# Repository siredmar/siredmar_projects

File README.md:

siredmar_projects
=================

edmar_projects

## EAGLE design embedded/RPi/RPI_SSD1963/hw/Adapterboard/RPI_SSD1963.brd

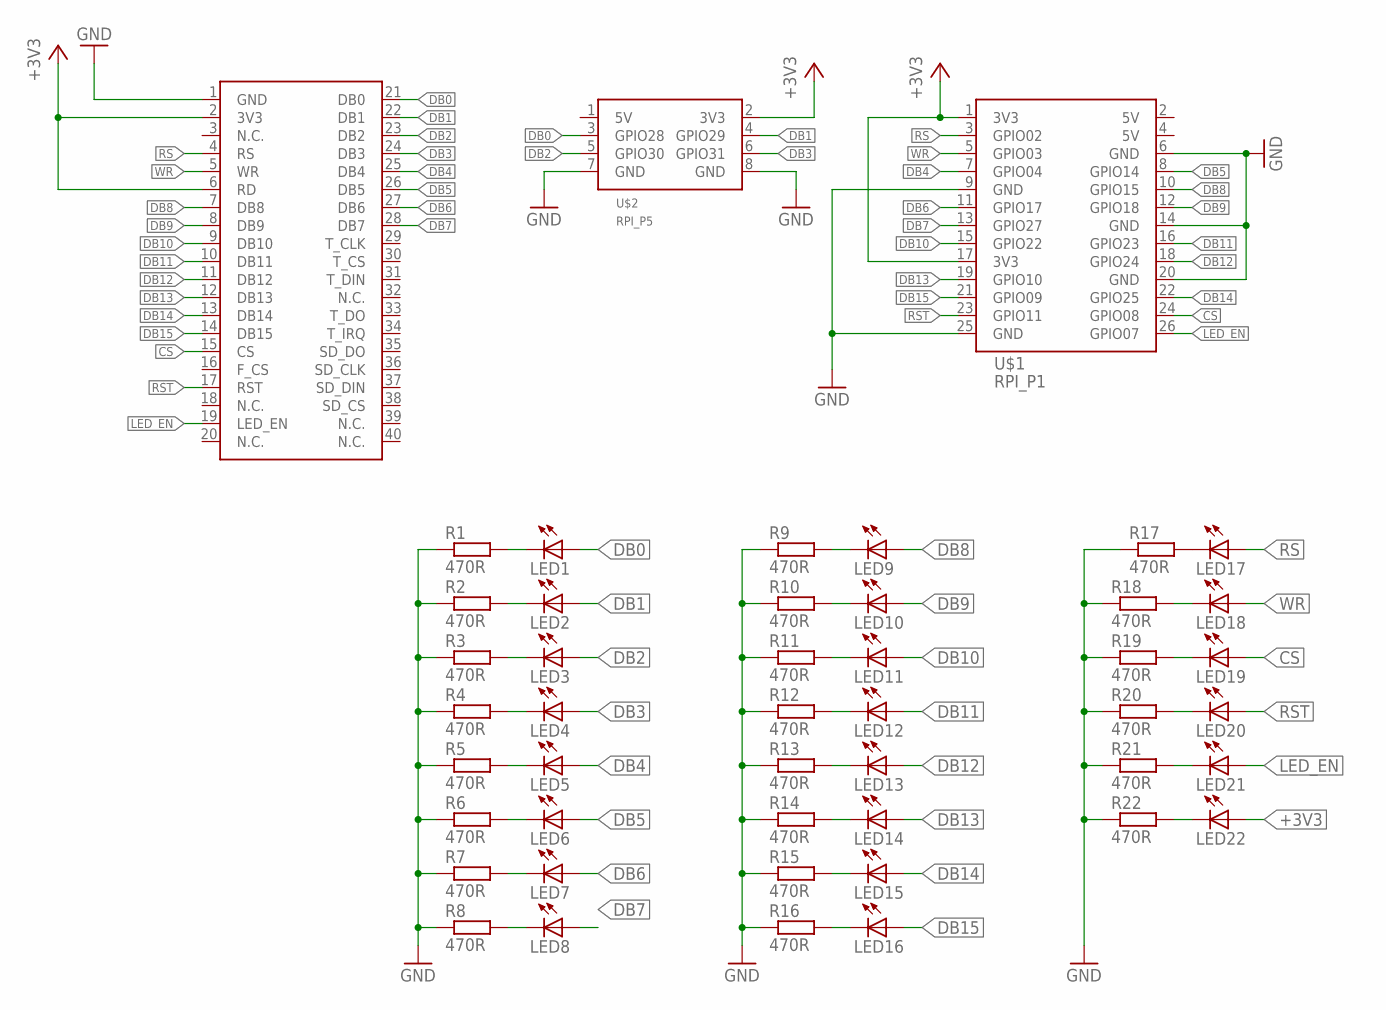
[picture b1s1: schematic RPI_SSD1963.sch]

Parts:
LED1, LED2, LED3, LED4, LED5, LED6, LED7, LED8, LED9, LED10, LED11, LED12, LED13, LED14, LED15, LED16, LED17, LED18, LED19, LED20, LED21, LED22: LEDCHIP-LED0603; CHIP-LED0603
R1, R2, R3, R4, R5, R6, R7, R8, R9, R10, R11, R12, R13, R14, R15, R16, R17, R18, R19, R20, R21, R22: 470R; R0402
U$1: RPI_P1
U$2: RPI_P5
U$3: SSD1963

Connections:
+3V3: LED22.A, U$1.1 (3V3), U$1.17 (3V3), U$2.2 (3V3), U$3.2 (3V3), U$3.6 (RD)
CS: LED19.A, U$1.24 (GPIO08), U$3.15 (CS)
DB0: LED1.A, U$2.3 (GPIO28), U$3.21 (DB0)
DB1: LED2.A, U$2.4 (GPIO29), U$3.22 (DB1)
DB2: LED3.A, U$2.5 (GPIO30), U$3.23 (DB2)
DB3: LED4.A, U$2.6 (GPIO31), U$3.24 (DB3)
DB4: LED5.A, U$1.7 (GPIO04), U$3.25 (DB4)
DB5: LED6.A, U$1.8 (GPIO14), U$3.26 (DB5)
DB6: LED7.A, U$1.11 (GPIO17), U$3.27 (DB6)
DB7: LED8.A, U$1.13 (GPIO27), U$3.28 (DB7)
DB8: LED9.A, U$1.10 (GPIO15), U$3.7 (DB8)
DB9: LED10.A, U$1.12 (GPIO18), U$3.8 (DB9)
DB10: LED11.A, U$1.15 (GPIO22), U$3.9 (DB10)
DB11: LED12.A, U$1.16 (GPIO23), U$3.10 (DB11)
DB12: LED13.A, U$1.18 (GPIO24), U$3.11 (DB12)
DB13: LED14.A, U$1.19 (GPIO10), U$3.12 (DB13)
DB14: LED15.A, U$1.22 (GPIO25), U$3.13 (DB14)
DB15: LED16.A, U$1.21 (GPIO09), U$3.14 (DB15)
GND: R1.1, R2.1, R3.1, R4.1, R5.1, R6.1, R7.1, R8.1, R9.1, R10.1, R11.1, R12.1, R13.1, R14.1, R15.1, R16.1, R17.1, R18.1, R19.1, R20.1, R21.1, R22.1, U$1.6 (GND), U$1.9 (GND), U$1.14 (GND), U$1.20 (GND), U$1.25 (GND), U$2.7 (GND), U$2.8 (GND), U$3.1 (GND)
LED_EN: LED21.A, U$1.26 (GPIO07), U$3.19 (LED_EN)
unnamed: LED1.C, R1.2
unnamed: LED2.C, R2.2
unnamed: LED3.C, R3.2
unnamed: LED4.C, R4.2
unnamed: LED5.C, R5.2
unnamed: LED6.C, R6.2
unnamed: LED7.C, R7.2
unnamed: LED8.C, R8.2
unnamed: LED9.C, R9.2
unnamed: LED10.C, R10.2
unnamed: LED11.C, R11.2
unnamed: LED12.C, R12.2
unnamed: LED13.C, R13.2
unnamed: LED14.C, R14.2
unnamed: LED15.C, R15.2
unnamed: LED16.C, R16.2
unnamed: LED17.C, R17.2
unnamed: LED18.C, R18.2
unnamed: LED19.C, R19.2
unnamed: LED20.C, R20.2
unnamed: LED21.C, R21.2
unnamed: LED22.C, R22.2
RS: LED17.A, U$1.3 (GPIO02), U$3.4 (RS)
RST: LED20.A, U$1.23 (GPIO11), U$3.17 (RST)
WR: LED18.A, U$1.5 (GPIO03), U$3.5 (WR)

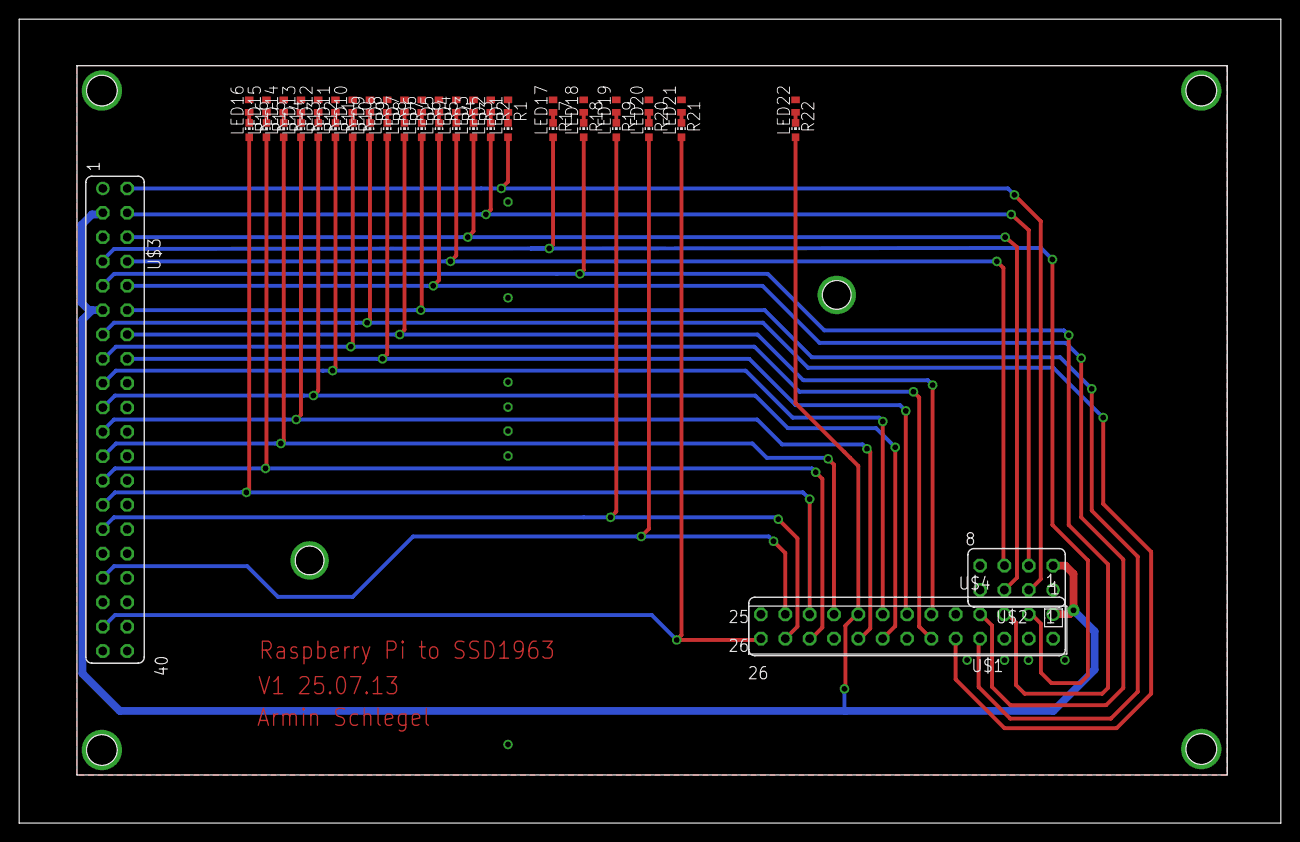
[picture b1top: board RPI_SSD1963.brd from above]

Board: 2 copper layers, 131.6 x 83.9 mm, 48 parts (0 on the bottom side), 45 nets.

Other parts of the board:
U$4: RPI_OUTLINE; RASP_OUTLINE

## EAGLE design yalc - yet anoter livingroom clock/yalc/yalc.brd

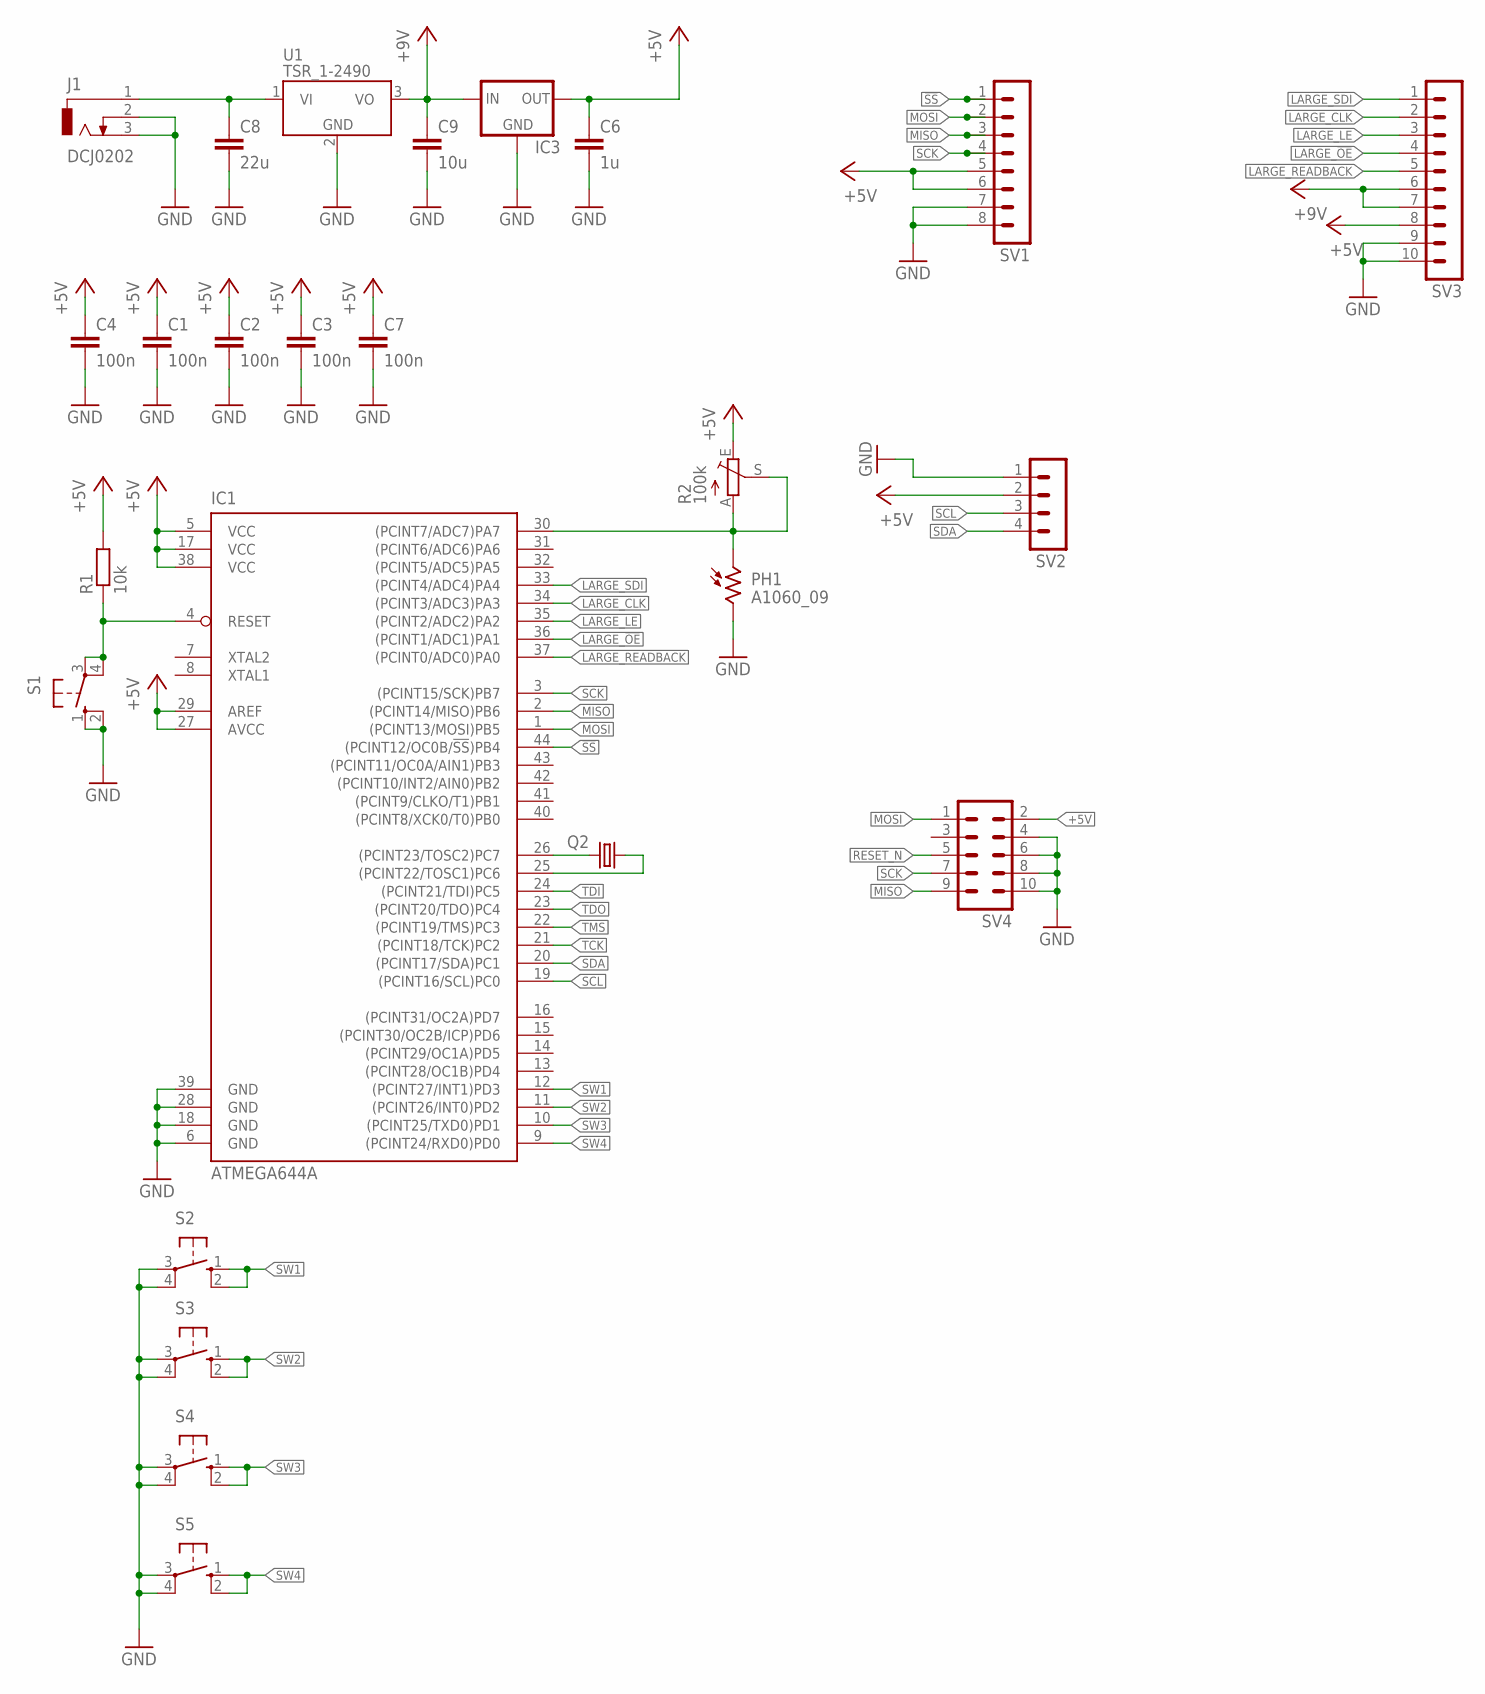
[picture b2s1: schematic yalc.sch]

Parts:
C1, C2, C3, C4, C7: 100n; C0805
C6: 1u; C1206K
C8: 22u; C1206K
C9: 10u; C1206K
IC1: ATMEGA644A; TQFP44
IC3: LFXXCVL; TO220L1
J1: DCJ0202
PH1: A1060_09; T0-46-A10XX
Q2: CRYSTALTC26H; TC26H
R1: 10k; R0805
R2: 100k; ECP10S
S1, S2, S3, S4, S5: 10-XX; B3F-10XX
SV1: MA08-1W
SV2: MA04-1
SV3: MA10-1W
SV4: ML10
U1: TSR_1-2490; TSR-1

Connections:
!SS: IC1.44 ((PCINT12/OC0B/!SS!)PB4), SV1.1
+5V: C1.1, C2.1, C3.1, C4.1, C6.1, C7.1, IC1.5 (VCC), IC1.17 (VCC), IC1.27 (AVCC), IC1.29 (AREF), IC1.38 (VCC), IC3.3 (OUT), R1.2, R2.E, SV1.5, SV1.6, SV2.2, SV3.8, SV4.2
+9V: C9.1, IC3.1 (IN), SV3.6, SV3.7, U1.3 (VO)
GND: C1.2, C2.2, C3.2, C4.2, C6.2, C7.2, C8.2, C9.2, IC1.6 (GND), IC1.18 (GND), IC1.28 (GND), IC1.39 (GND), IC3.2 (GND), J1.2, J1.3, PH1.2, S1.1 (S), S1.2 (S1), S2.3, S2.4 (P1), S3.3, S3.4 (P1), S4.3, S4.4 (P1), S5.3, S5.4 (P1), SV1.7, SV1.8, SV2.1, SV3.9, SV3.10, SV4.4, SV4.6, SV4.8, SV4.10, U1.2 (GND)
LARGE_!OE: IC1.36 ((PCINT1/ADC1)PA1), SV3.4
LARGE_CLK: IC1.34 ((PCINT3/ADC3)PA3), SV3.2
LARGE_LE: IC1.35 ((PCINT2/ADC2)PA2), SV3.3
LARGE_READBACK: IC1.37 ((PCINT0/ADC0)PA0), SV3.5
LARGE_SDI: IC1.33 ((PCINT4/ADC4)PA4), SV3.1
MISO: IC1.2 ((PCINT14/MISO)PB6), SV1.3, SV4.9
MOSI: IC1.1 ((PCINT13/MOSI)PB5), SV1.2, SV4.1
unnamed: IC1.30 ((PCINT7/ADC7)PA7), PH1.1, R2.A, R2.S
unnamed: IC1.26 ((PCINT23/TOSC2)PC7), Q2.2
unnamed: IC1.25 ((PCINT22/TOSC1)PC6), Q2.1
RESET_N: IC1.4 (RESET), R1.1, S1.3, S1.4 (P1), SV4.5
SCK: IC1.3 ((PCINT15/SCK)PB7), SV1.4, SV4.7
SCL: IC1.19 ((PCINT16/SCL)PC0), SV2.3
SDA: IC1.20 ((PCINT17/SDA)PC1), SV2.4
SW1: IC1.12 ((PCINT27/INT1)PD3), S2.1 (S), S2.2 (S1)
SW2: IC1.11 ((PCINT26/INT0)PD2), S3.1 (S), S3.2 (S1)
SW3: IC1.10 ((PCINT25/TXD0)PD1), S4.1 (S), S4.2 (S1)
SW4: IC1.9 ((PCINT24/RXD0)PD0), S5.1 (S), S5.2 (S1)
TCK: IC1.21 ((PCINT18/TCK)PC2)
TDI: IC1.24 ((PCINT21/TDI)PC5)
TDO: IC1.23 ((PCINT20/TDO)PC4)
TMS: IC1.22 ((PCINT19/TMS)PC3)
VI: C8.1, J1.1, U1.1 (VI)

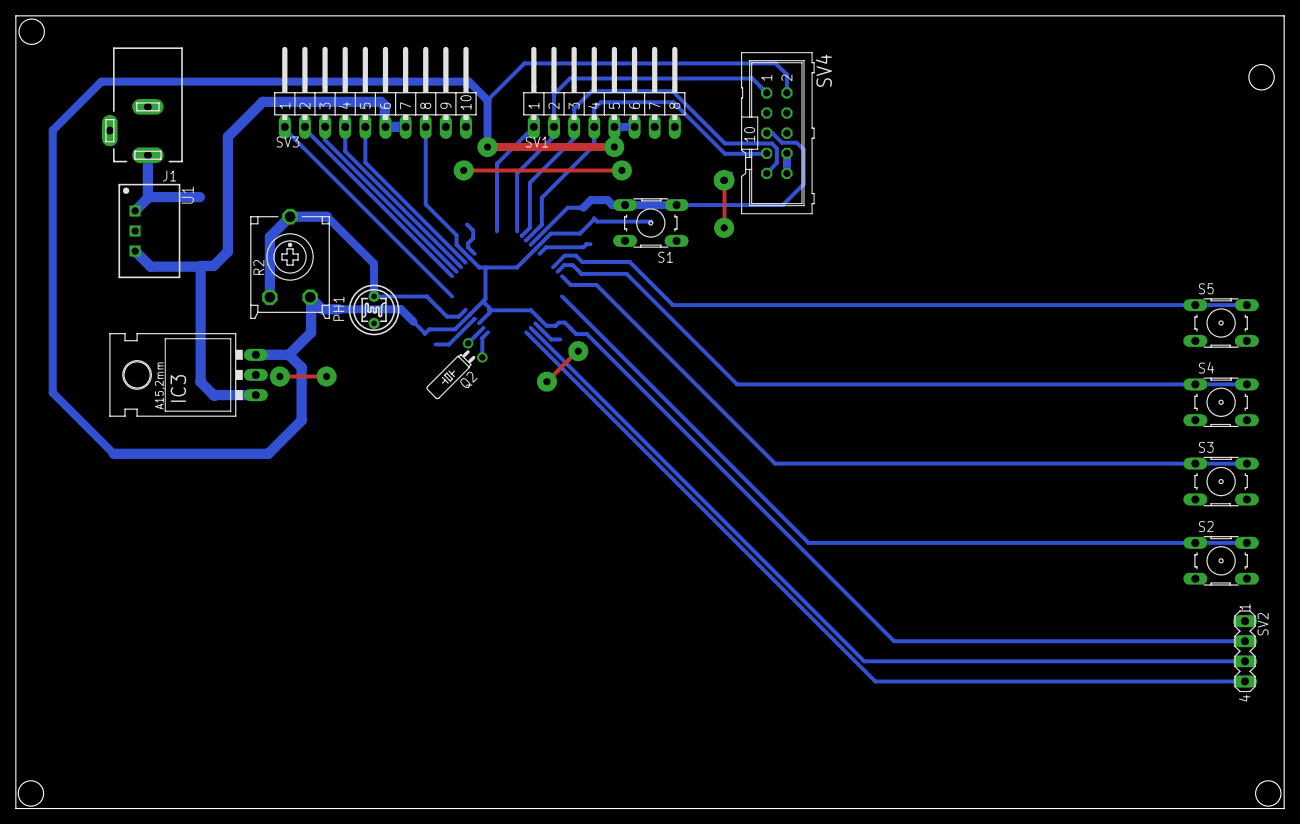
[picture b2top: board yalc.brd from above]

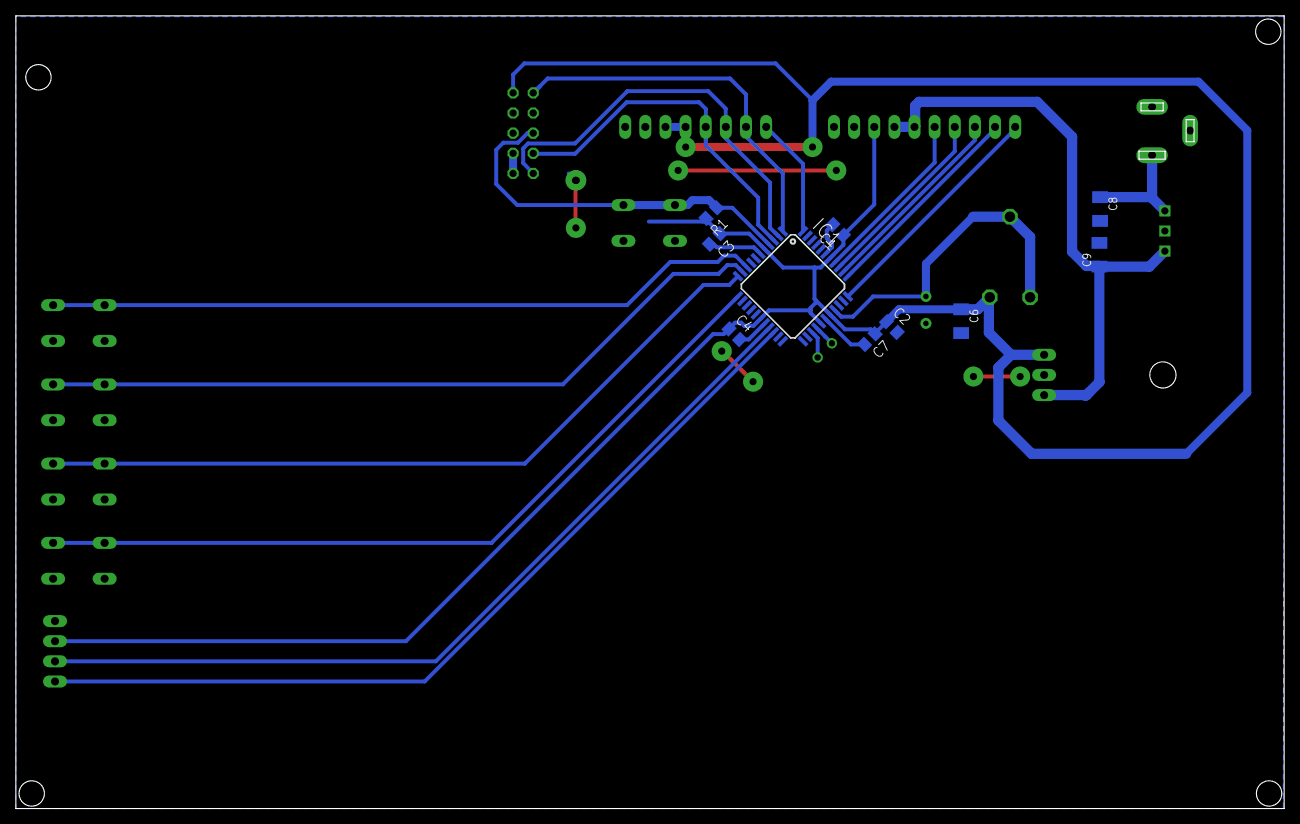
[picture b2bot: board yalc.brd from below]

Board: 2 copper layers, 160.0 x 100.0 mm, 25 parts (10 on the bottom side), 23 nets.

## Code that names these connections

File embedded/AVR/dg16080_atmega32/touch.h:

/**
 * touch.h
 *
 *  Created on: 29.05.2009
 *      Author: sebastian
 */

#ifndef TOUCH_H_
#define TOUCH_H_ TOUCH_H_

#include "adc.h"


#define TOUCH_PORT 	PORTA
#define TOUCH_PIN	PINA
#define TOUCH_DDR  	DDRA

#define TOUCH_X1 PA0
#define TOUCH_X2 PA1
#define TOUCH_Y1 PA2
#define TOUCH_Y2 PA3

#define TOUCH_PRESSED_LEVEL 1000

uint8_t touch_is_pressed(void);

int16_t touch_readX(void);
int16_t touch_readY(void);

#endif /* TOUCH_H_ */

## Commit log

2014-06-16 first commit of schematic and layout of base board
2014-06-18 moved yalc to repo of Mister-L
2014-06-25 merged many svn and cvs repos to this one git repo
2014-06-25 deleted local yalc repo due it's move to Mister-L's repo
2014-07-09 added some
